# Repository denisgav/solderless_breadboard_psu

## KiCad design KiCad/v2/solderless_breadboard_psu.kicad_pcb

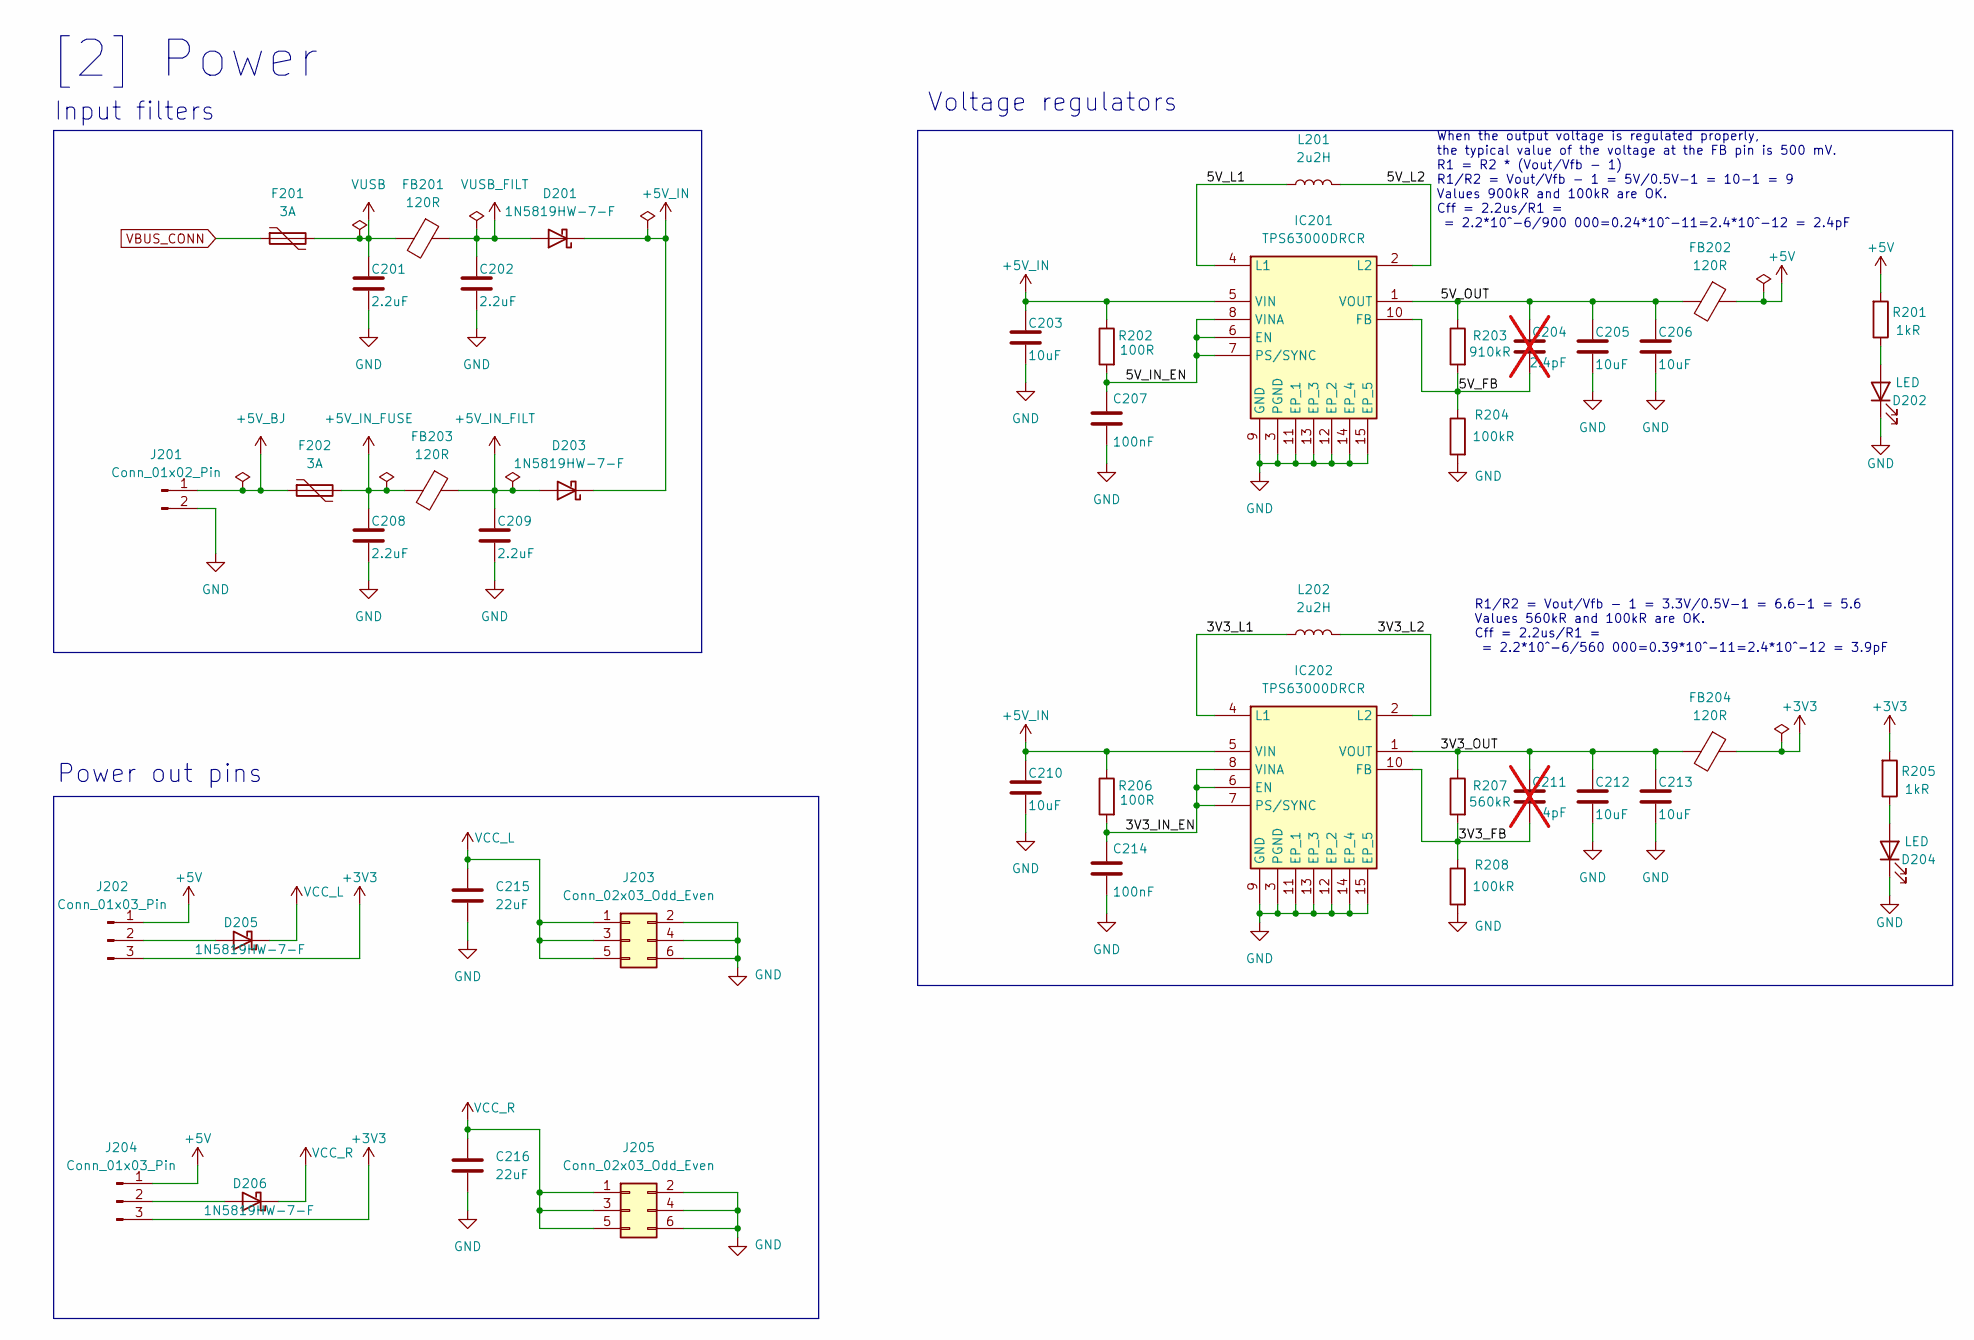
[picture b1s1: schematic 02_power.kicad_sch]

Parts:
C201, C202, C208, C209: 2.2uF; C_0603_1608Metric; Manufacturer Part Number CL10A225KO8NNNC; LCSC Part Number C23630
C203, C205, C206, C210, C212, C213: 10uF; C_0603_1608Metric; Manufacturer Part Number GRM188R61E106MA73D; LCSC Part Number C91606
C204: 2.4pF; C_0603_1608Metric; Manufacturer Part Number CC0603BRNPO9BN2R4; LCSC Part Number C519102; not fitted
C207, C214: 100nF; C_0402_1005Metric; Manufacturer Part Number GCM155R71H104KE02D; LCSC Part Number C85858
C211: 4pF; C_0603_1608Metric; not fitted
C215, C216: 22uF; C_0603_1608Metric; Manufacturer Part Number CL10A226MP8NUNE; DigiKey Part Number 1276-6687-6-ND
D201, D203, D205, D206: 1N5819HW-7-F; D_SOD-123; Manufacturer Part Number 1N5819HW-7-F; LCSC Part Number C82544
D202, D204: LED; LED_0603_1608Metric; Manufacturer Part Number XL-1608SURC-06; LCSC Part Number C965799
F201, F202: 3A; Fuse_0805_2012Metric; Manufacturer Part Number BSMD0805-100-6V; LCSC Part Number C883112
FB201, FB202, FB203, FB204: 120R; Fuse_0603_1608Metric; Manufacturer Part Number BLM18PG121SN1D; LCSC Part Number C14709
IC201, IC202: TPS63000DRCR; TPS63002DRCR; Manufacturer_Part_Number TPS63000DRCR; Mouser Part Number 595-TPS63000DRCR
J201: Conn_01x02_Pin; PinHeader_1x02_P2.54mm_Vertical
J202, J204: Conn_01x03_Pin; PinHeader_1x03_P2.54mm_Vertical
J203, J205: Conn_02x03_Odd_Even; PinHeader_2x03_P2.54mm_Vertical
L201, L202: 2u2H; L_Changjiang_FXL0630; Manufacturer Part Number FXL0630-2R2-M; LCSC Part Number C167218
R201, R205: 1kR; R_0402_1005Metric; Manufacturer Part Number RC0402FR-071KL; LCSC Part Number C106235
R202, R206: 100R; R_0402_1005Metric; Manufacturer Part Number RT0402BRD07100RL; LCSC Part Number C705627
R203: 910kR; R_0402_1005Metric; Manufacturer Part Number FRC0402F9103TS; LCSC Part Number C2909391
R204, R208: 100kR; R_0402_1005Metric; Manufacturer Part Number RT0402BRD07100KL; LCSC Part Number C852472
R207: 560kR; R_0402_1005Metric; Manufacturer Part Number 0402WGF5603TCE; LCSC Part Number C132339

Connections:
+3V3: FB204.1, J202.3, J204.3, R205.2
+5V: FB202.1, J202.1, J204.1, R201.2
+5V_BJ: F202.1, J201.1
+5V_IN: C203.1, C210.1, D201.1 (K), D203.1 (K), IC201.5 (VIN), IC202.5 (VIN), R202.1, R206.1
+5V_IN_FILT: C209.1, D203.2 (A), FB203.1
+5V_IN_FUSE: C208.1, F202.2, FB203.2
/[2] Power/3V3_FB: C211.2, IC202.10 (FB), R207.2, R208.1
/[2] Power/3V3_IN_EN: C214.1, IC202.6 (EN), IC202.7 (PS/SYNC), IC202.8 (VINA), R206.2
/[2] Power/3V3_L1: IC202.4 (L1), L202.1
/[2] Power/3V3_L2: IC202.2 (L2), L202.2
/[2] Power/3V3_OUT: C211.1, C212.1, C213.1, FB204.2, IC202.1 (VOUT), R207.1
/[2] Power/5V_FB: C204.2, IC201.10 (FB), R203.2, R204.1
/[2] Power/5V_IN_EN: C207.1, IC201.6 (EN), IC201.7 (PS/SYNC), IC201.8 (VINA), R202.2
/[2] Power/5V_L1: IC201.4 (L1), L201.1
/[2] Power/5V_L2: IC201.2 (L2), L201.2
/[2] Power/5V_OUT: C204.1, C205.1, C206.1, FB202.2, IC201.1 (VOUT), R203.1
GND: C201.2, C202.2, C203.2, C205.2, C206.2, C207.2, C208.2, C209.2, C210.2, C212.2, C213.2, C214.2, C215.2, C216.2, D202.1 (K), D204.1 (K), IC201.3 (PGND), IC201.9 (GND), IC201.11 (EP_1), IC201.12 (EP_2), IC201.13 (EP_3), IC201.14 (EP_4), IC201.15 (EP_5), IC202.3 (PGND), IC202.9 (GND), IC202.11 (EP_1), IC202.12 (EP_2), IC202.13 (EP_3), IC202.14 (EP_4), IC202.15 (EP_5), J201.2, J203.2, J203.4, J203.6, J205.2, J205.4, J205.6, R204.2, R208.2; also elsewhere on the board
unnamed: D202.2 (A), R201.1
unnamed: D204.2 (A), R205.1
unnamed: D205.2 (A), J202.2
unnamed: D206.2 (A), J204.2
VBUS_CONN: F201.1; also elsewhere on the board
VCC_L: C215.1, D205.1 (K), J203.1, J203.3, J203.5
VCC_R: C216.1, D206.1 (K), J205.1, J205.3, J205.5
VUSB: C201.1, F201.2, FB201.2; also elsewhere on the board
VUSB_FILT: C202.1, D201.2 (A), FB201.1; also elsewhere on the board

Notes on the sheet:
Input filters
Voltage regulators
When the output voltage is regulated properly, the typical value of the voltage at the FB pin is 500 mV. R1 = R2 * (Vout/Vfb - 1) R1/R2 = Vout/Vfb - 1 = 5V/0.5V-1 = 10-1 = 9 Values 900kR and 100kR are OK. Cff = 2.2us/R1 = = 2.2*10^-6/900 000=0.24*10^-11=2.4*10^-12 = 2.4pF
[2] Power
Power out pins
R1/R2 = Vout/Vfb - 1 = 3.3V/0.5V-1 = 6.6-1 = 5.6 Values 560kR and 100kR are OK. Cff = 2.2us/R1 = = 2.2*10^-6/560 000=0.39*10^-11=2.4*10^-12 = 3.9pF

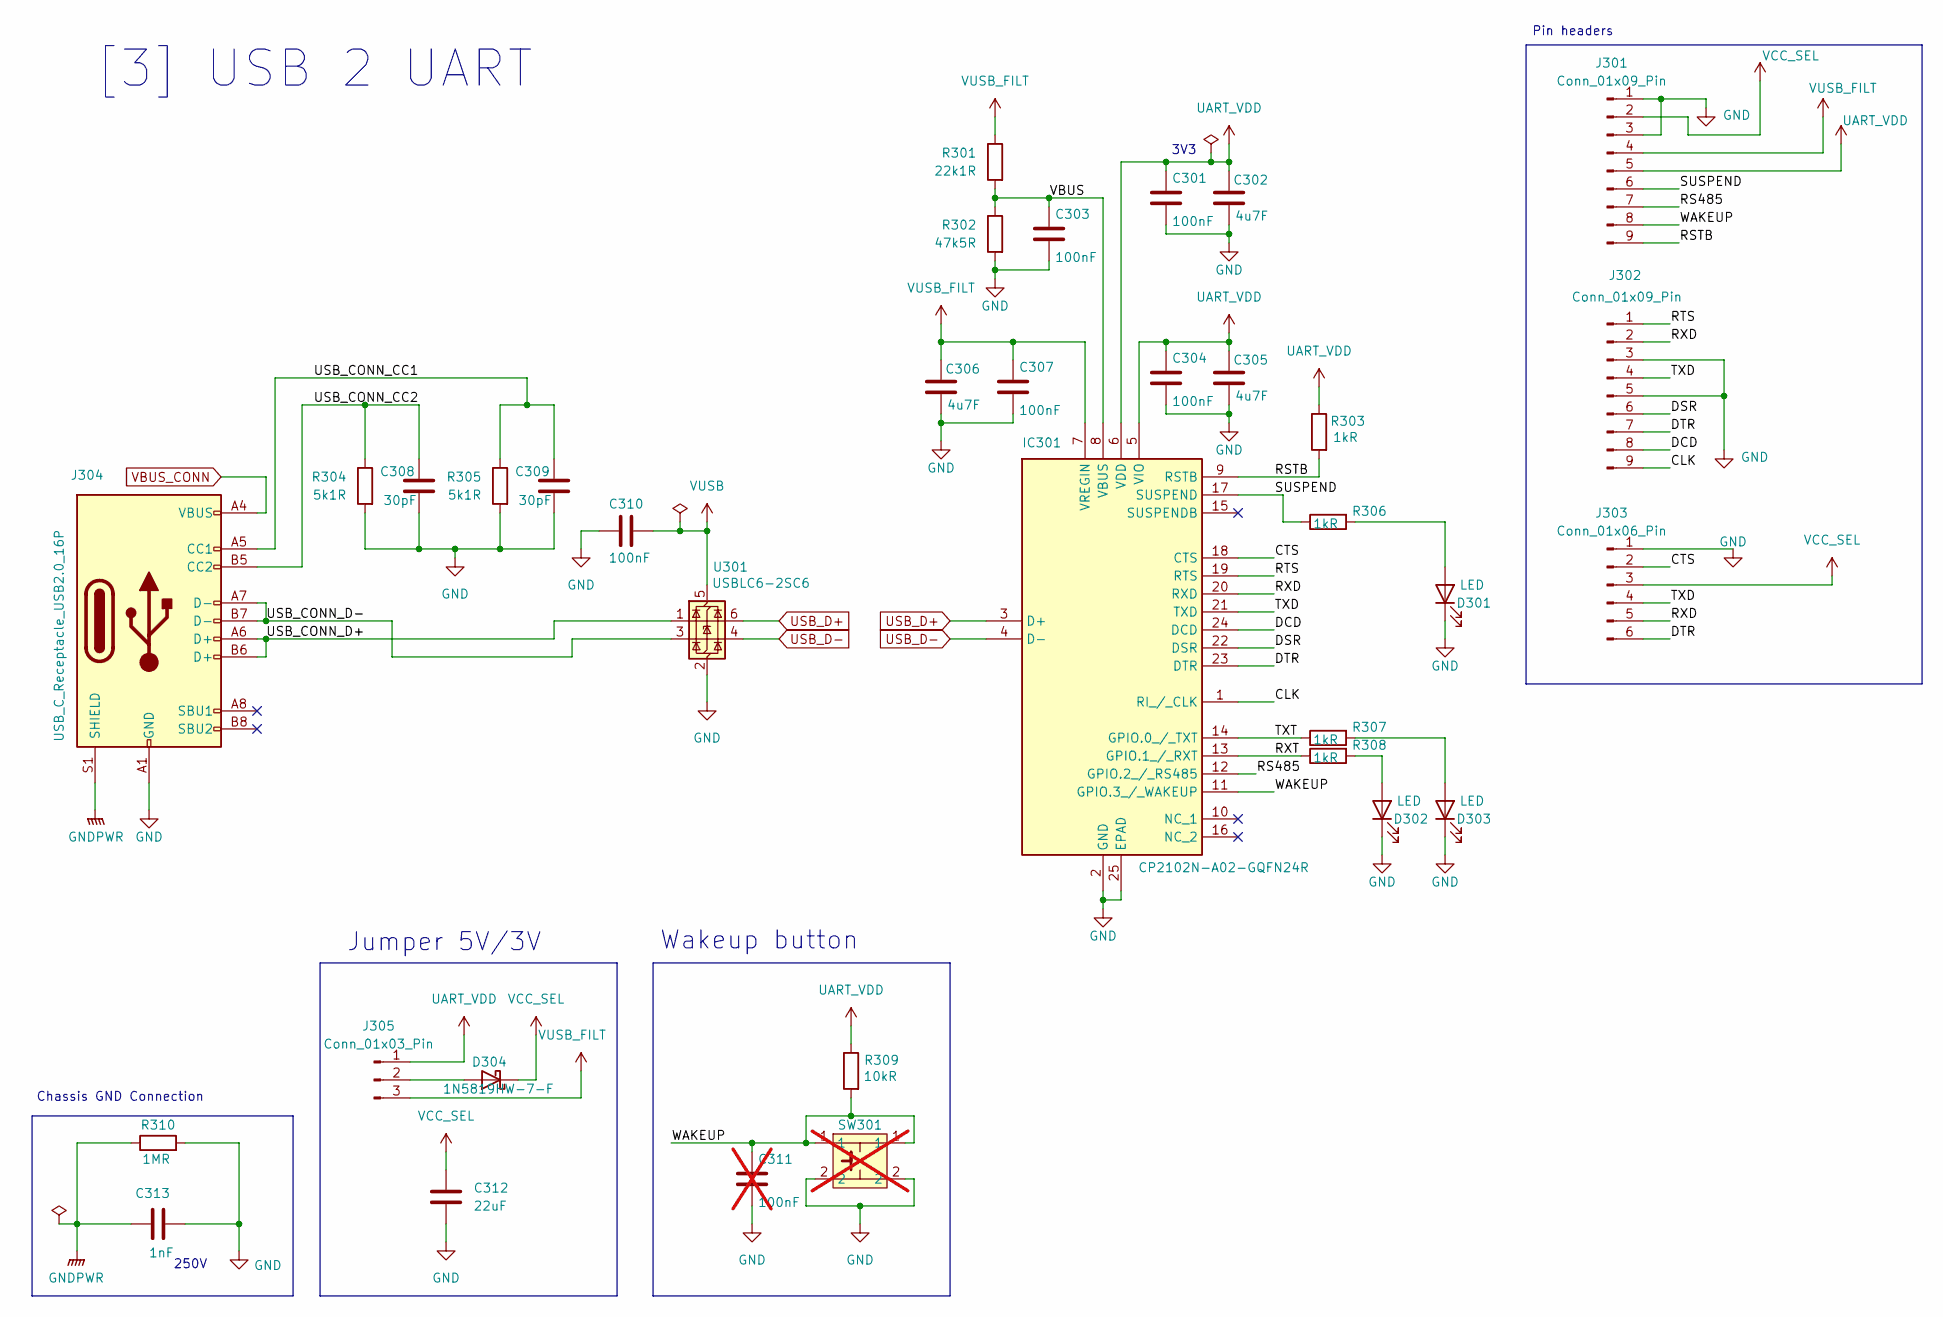
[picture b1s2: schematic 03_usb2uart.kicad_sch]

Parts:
C301, C303, C304, C307, C310: 100nF; C_0402_1005Metric; Manufacturer Part Number GCM155R71H104KE02D; LCSC Part Number C85858
C302, C305, C306: 4u7F; C_0603_1608Metric; Manufacturer Part Number CL10A475KP8NNNC; LCSC Part Number C1705
C308, C309: 30pF; C_0603_1608Metric; Manufacturer Part Number CC0603JRNPO9BN300; LCSC Part Number C113797
C311: 100nF; C_0402_1005Metric; Manufacturer Part Number GCM155R71H104KE02D; LCSC Part Number C85858; not fitted
C312: 22uF; C_0603_1608Metric; Manufacturer Part Number CL10A226MP8NUNE; DigiKey Part Number 1276-6687-6-ND
C313: 1nF; C_0603_1608Metric; Manufacturer Part Number CC0603KRX7R9BB102; LCSC Part Number C100040
D301, D302, D303: LED; LED_0603_1608Metric; Manufacturer Part Number XL-1608SURC-06; LCSC Part Number C965799
D304: 1N5819HW-7-F; D_SOD-123; Manufacturer Part Number 1N5819HW-7-F; LCSC Part Number C82544
IC301: CP2102N-A02-GQFN24R; QFN50P400X400X80-25N-D; Manufacturer_Part_Number CP2102N-A02-GQFN24R; Mouser Part Number 634-CP2102NA02QFN24R
J301, J302: Conn_01x09_Pin; PinHeader_1x09_P2.54mm_Vertical
J303: Conn_01x06_Pin; PinHeader_1x06_P2.54mm_Vertical
J304: USB_C_Receptacle_USB2.0_16P; USB_C_Receptacle_HCTL_HC-TYPE-C-16P-01A; Manufacturer Part Number TYPE-C-31-M-12; LCSC Part Number C165948
J305: Conn_01x03_Pin; PinHeader_1x03_P2.54mm_Vertical
R301: 22k1R; R_0402_1005Metric; Manufacturer Part Number CRCW040222K1FKED; LCSC Part Number C844504
R302: 47k5R; R_0402_1005Metric; Manufacturer Part Number RT0402DRE0747K5L; LCSC Part Number C853963
R303, R306, R307, R308: 1kR; R_0402_1005Metric; Manufacturer Part Number RC0402FR-071KL; LCSC Part Number C106235
R304, R305: 5k1R; R_0402_1005Metric; Manufacturer Part Number RT0402BRD075K1L; LCSC Part Number C852856
R309: 10kR; R_0402_1005Metric; Manufacturer Part Number CQ02WGF1002TCE; LCSC Part Number C2765610
R310: 1MR; R_0402_1005Metric; Manufacturer Part Number RE0402BRE071ML; LCSC Part Number C1883577
SW301: SW_PUSH_6mm_H5mm; Manufacturer Part Number SMG-01-H080A1; LCSC Part Number C29781314; not fitted
U301: USBLC6-2SC6; SOT-23-6; Manufacturer Part Number USBLC6-2SC6; LCSC Part Number C7519

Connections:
/[3] USB 2 UART/CLK: IC301.1 (RI_/_CLK), J302.9
/[3] USB 2 UART/CTS: IC301.18 (CTS), J303.2
/[3] USB 2 UART/DCD: IC301.24 (DCD), J302.8
/[3] USB 2 UART/DSR: IC301.22 (DSR), J302.6
/[3] USB 2 UART/DTR: IC301.23 (DTR), J302.7, J303.6
/[3] USB 2 UART/RS485: IC301.12 (GPIO.2_/_RS485), J301.7
/[3] USB 2 UART/RSTB: IC301.9 (RSTB), J301.9, R303.2
/[3] USB 2 UART/RTS: IC301.19 (RTS), J302.1
/[3] USB 2 UART/RXD: IC301.20 (RXD), J302.2, J303.5
/[3] USB 2 UART/RXT: IC301.13 (GPIO.1_/_RXT), R308.1
/[3] USB 2 UART/SUSPEND: IC301.17 (SUSPEND), J301.6, R306.1
/[3] USB 2 UART/TXD: IC301.21 (TXD), J302.4, J303.4
/[3] USB 2 UART/TXT: IC301.14 (GPIO.0_/_TXT), R307.1
/[3] USB 2 UART/USB_CONN_CC1: C309.1, J304.A5 (CC1), R305.1
/[3] USB 2 UART/USB_CONN_CC2: C308.1, J304.B5 (CC2), R304.1
/[3] USB 2 UART/USB_CONN_D+: J304.A6 (D+), J304.B6 (D+), U301.1 (I/O1)
/[3] USB 2 UART/USB_CONN_D-: J304.A7 (D-), J304.B7 (D-), U301.3 (I/O2)
/[3] USB 2 UART/VBUS: C303.1, IC301.8 (VBUS), R301.2, R302.1
/[3] USB 2 UART/WAKEUP: C311.1, IC301.11 (GPIO.3_/_WAKEUP), J301.8, R309.2, SW301.1
GND: C301.2, C302.2, C303.2, C304.2, C305.2, C306.2, C307.2, C308.2, C309.2, C310.2, C311.2, C312.2, C313.2, D301.1 (K), D302.1 (K), D303.1 (K), IC301.2 (GND), IC301.25 (EPAD), J301.1, J301.3, J302.3, J302.5, J303.1, J304.A1 (GND), J304.A12 (GND), J304.B1 (GND), J304.B12 (GND), R302.2, R304.2, R305.2, R310.2, SW301.2, U301.2 (GND); also elsewhere on the board
GNDPWR: C313.1, J304.S1 (SHIELD), R310.1
unnamed: D301.2 (A), R306.2
unnamed: D302.2 (A), R308.2
unnamed: D303.2 (A), R307.2
unnamed: D304.2 (A), J305.2
UART_VDD: C301.1, C302.1, C304.1, C305.1, IC301.5 (VIO), IC301.6 (VDD), J301.5, J305.1, R303.1, R309.1
USB_D+: IC301.3 (D+), U301.6 (I/O1)
USB_D-: IC301.4 (D-), U301.4 (I/O2)
VBUS_CONN: J304.A4 (VBUS), J304.A9 (VBUS), J304.B4 (VBUS), J304.B9 (VBUS); also elsewhere on the board
VCC_SEL: C312.1, D304.1 (K), J301.2, J303.3
VUSB: C310.1, U301.5 (VBUS); also elsewhere on the board
VUSB_FILT: C306.1, C307.1, IC301.7 (VREGIN), J301.4, J305.3, R301.1; also elsewhere on the board

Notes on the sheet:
Jumper 5V/3V
3V3
Pin headers
Wakeup button
Chassis GND Connection
250V
[3] USB 2 UART

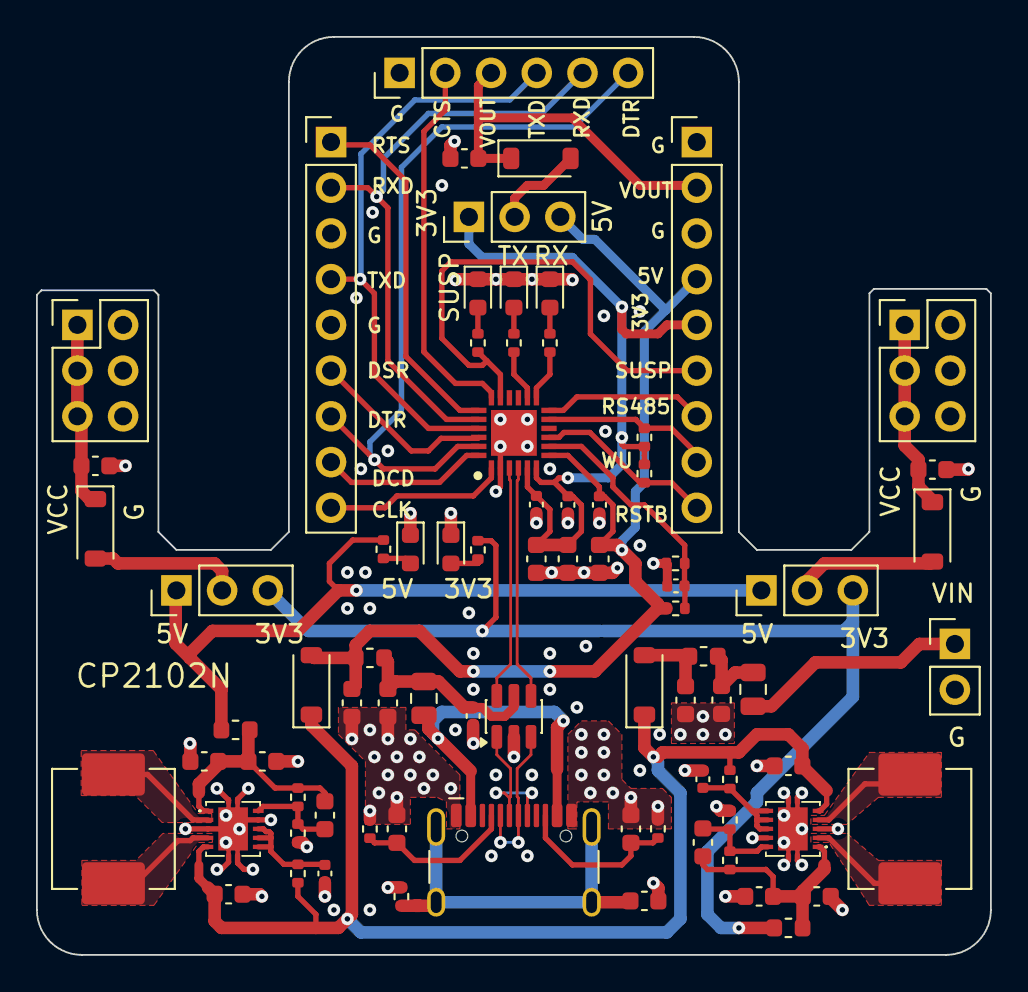
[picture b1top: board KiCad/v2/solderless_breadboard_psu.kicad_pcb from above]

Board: 4 copper layers, 53.0 x 51.0 mm, 78 parts (0 on the bottom side), 54 nets.

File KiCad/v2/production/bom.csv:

Designator,Footprint,Quantity,Value,LCSC Part #
"C201, C202, C208, C209",0603,4,2.2uF,C23630
"C203, C205, C206, C210, C212, C213",0603,6,10uF,C91606
C204,0603,1,2.4pF,C113797
"C207, C214, C301, C303, C304, C307, C310",0402,7,100nF,C126532
C211,0603,1,4pF,
"C215, C216, C312",0603,3,22uF,C86295
"C302, C305, C306",0603,3,4u7F,C1705
"C308, C309",0603,2,30pF,C113797
C313,0603,1,1nF,C277510
"D201, D203, D205, D206, D304",D_SOD-123,5,1N5819HW-7-F,C82544
"D202, D204, D301, D302, D303",0603,5,LED,C965799
"F201, F202",0805,2,3A,C883112
"FB201, FB202, FB203, FB204",0603,4,120R,C14709
"IC201, IC202",TPS63002DRCR,2,TPS63000DRCR,C116655
IC301,QFN50P400X400X80-25N-D,1,CP2102N-A02-GQFN24R,C969151
J201,PinHeader_1x02_P2.54mm_Vertical,1,Conn_01x02_Pin,
"J202, J204, J305",PinHeader_1x03_P2.54mm_Vertical,3,Conn_01x03_Pin,
"J203, J205",PinHeader_2x03_P2.54mm_Vertical,2,Conn_02x03_Odd_Even,
"J301, J302",PinHeader_1x09_P2.54mm_Vertical,2,Conn_01x09_Pin,
J303,PinHeader_1x06_P2.54mm_Vertical,1,Conn_01x06_Pin,
J304,USB_C_Receptacle_HCTL_HC-TYPE-C-16P-01A,1,USB_C_Receptacle_USB2.0_16P,C165948
"L201, L202",L_Changjiang_FXL0630,2,2u2H,C167218
"R201, R205, R303, R306, R307, R308",0402,6,1kR,C106235
"R202, R206",0402,2,100R,C705627
R203,0402,1,910kR,C2909391
"R204, R208",0402,2,100kR,C852472
R207,0402,1,560kR,C132339
R301,0402,1,22k1R,C844504
R302,0402,1,47k5R,C853963
"R304, R305",0402,2,5k1R,C852856
R309,0402,1,10kR,C2765610
R310,0402,1,1MR,C1883577
U301,SOT-23-6,1,USBLC6-2SC6,C7519

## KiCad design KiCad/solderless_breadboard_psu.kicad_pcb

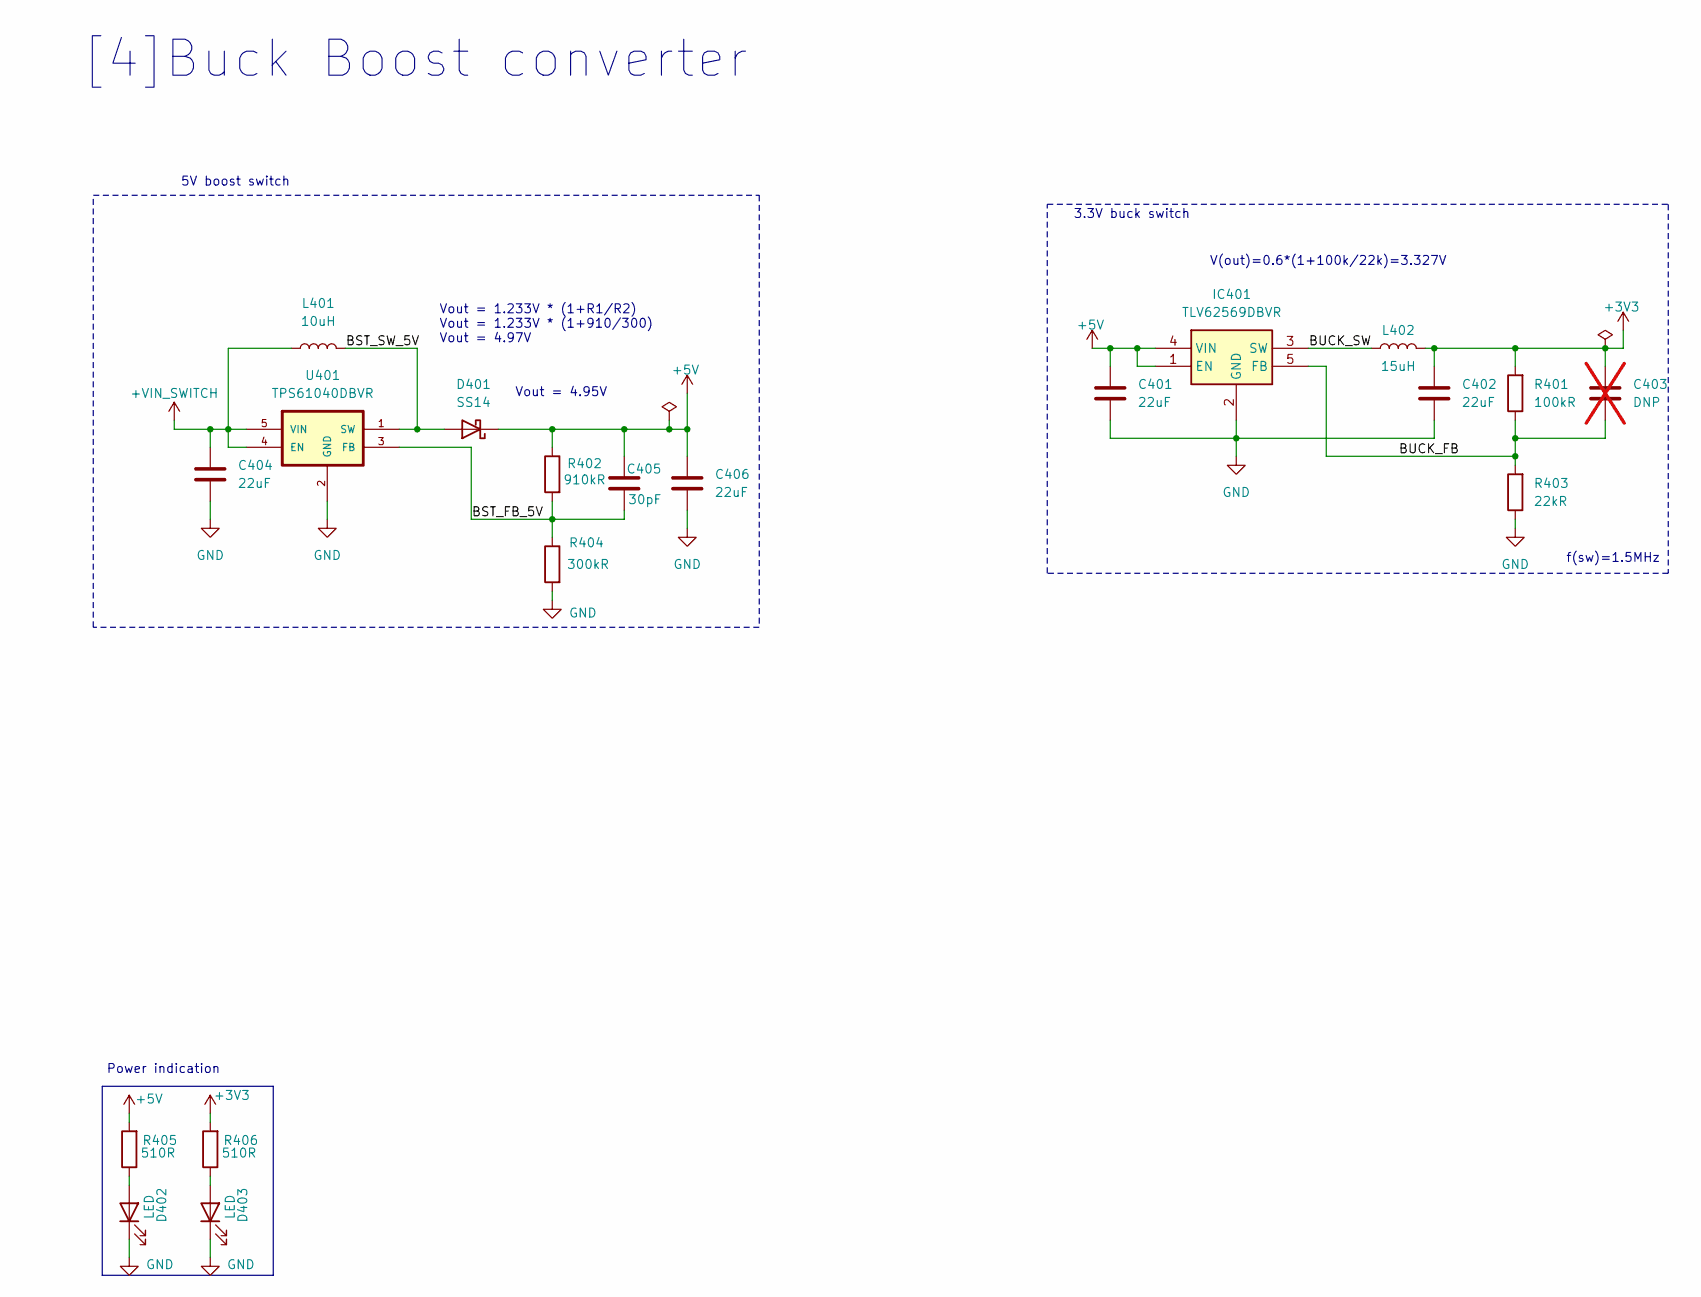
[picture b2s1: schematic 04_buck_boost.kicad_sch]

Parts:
C401, C402, C404, C406: 22uF; C_0603_1608Metric; Manufacturer Part Number CL10A226MP8NUNE; DigiKey Part Number 1276-6687-6-ND
C403: DNP; C_0402_1005Metric; not fitted
C405: 30pF; C_0603_1608Metric; Manufacturer Part Number CC0603JRNPO9BN300
D401: SS14; D_0603_1608Metric; Manufacturer Part Number SD0603S040S0R2
D402, D403: LED; LED_0603_1608Metric; Manufacturer Part Number XL-1608SURC-06
IC401: TLV62569DBVR; SOT95P280X145-5N; Manufacturer Part Number TLV62569DBVR
L401: 10uH; L_Changjiang_FXL0630; Manufacturer Part Number FXL0630-100-M
L402: 15uH; L_Changjiang_FXL0630; Manufacturer Part Number FXL0630-150-M; DigiKey Part Number 3442-MWSA0603S-150MTDKR-ND
R401: 100kR; R_0402_1005Metric; Manufacturer Part Number 0402WGF1003TCE; DigiKey Part Number P100KLDKR-ND
R402: 910kR; R_0402_1005Metric; Manufacturer Part Number 0402WGJ0914TCE
R403: 22kR; R_0402_1005Metric; Manufacturer Part Number 0402WGF2202TCE; DigiKey Part Number P22.0KLDKR-ND
R404: 300kR; R_0402_1005Metric; Manufacturer Part Number 0402WGF3003TCE
R405, R406: 510R; R_0402_1005Metric; Manufacturer Part Number 0402WGF5100TCE
U401: TPS61040DBVR; Manufacturer Part Number TPS61040DBVR

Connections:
+3V3: C402.1, C403.1, L402.2, R401.2, R406.2; also elsewhere on the board
+5V: C401.1, C405.1, C406.1, D401.1 (K), IC401.1 (EN), IC401.4 (VIN), R402.1, R405.2; also elsewhere on the board
+VIN_SWITCH: C404.1, L401.1, U401.4 (EN), U401.5 (VIN); also elsewhere on the board
/[4]Buck Boost converter/BST_FB_5V: C405.2, R402.2, R404.1, U401.3 (FB)
/[4]Buck Boost converter/BST_SW_5V: D401.2 (A), L401.2, U401.1 (SW)
/[4]Buck Boost converter/BUCK_FB: C403.2, IC401.5 (FB), R401.1, R403.2
/[4]Buck Boost converter/BUCK_SW: IC401.3 (SW), L402.1
GND: C401.2, C402.2, C404.2, C406.2, D402.1 (K), D403.1 (K), IC401.2 (GND), R403.1, R404.2, U401.2 (GND); also elsewhere on the board
unnamed: D402.2 (A), R405.1
unnamed: D403.2 (A), R406.1

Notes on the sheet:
Vout = 1.233V * (1+R1/R2) Vout = 1.233V * (1+910/300) Vout = 4.97V
[4]Buck Boost converter
Vout = 4.95V
3.3V buck switch
Power indication
V(out)=0.6*(1+100k/22k)=3.327V
f(sw)=1.5MHz
5V boost switch

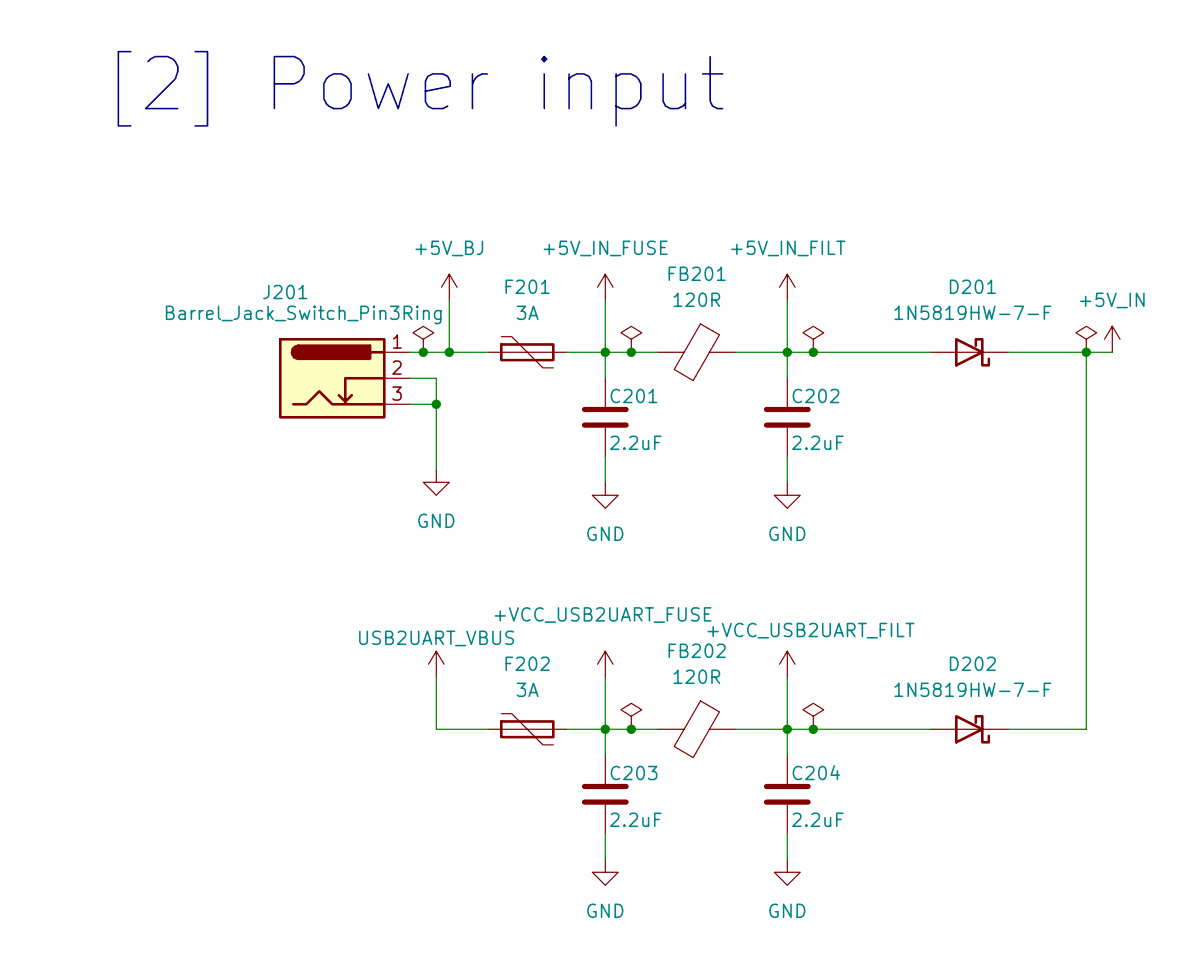
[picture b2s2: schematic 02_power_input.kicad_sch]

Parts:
C201, C202, C203, C204: 2.2uF; C_0603_1608Metric; Manufacturer Part Number CL10A225KO8NNNC
D201, D202: 1N5819HW-7-F; D_SOD-123; Manufacturer Part Number 1N5819HW-7-F
F201, F202: 3A; Fuse_0805_2012Metric; Manufacturer Part Number BSMD0805-100-6V
FB201, FB202: 120R; Fuse_0603_1608Metric; Manufacturer Part Number BLM18PG121SN1D
J201: Barrel_Jack_Switch_Pin3Ring; BarrelJack_GCT_DCJ200-10-A_Horizontal; Manufacturer Part Number DC005

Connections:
+5V_BJ: F201.1, J201.1
+5V_IN: D201.1 (K), D202.1 (K); also elsewhere on the board
+5V_IN_FILT: C202.1, D201.2 (A), FB201.1
+5V_IN_FUSE: C201.1, F201.2, FB201.2
+VCC_USB2UART_FILT: C204.1, D202.2 (A), FB202.1; also elsewhere on the board
+VCC_USB2UART_FUSE: C203.1, F202.2, FB202.2
GND: C201.2, C202.2, C203.2, C204.2, J201.2, J201.3; also elsewhere on the board
USB2UART_VBUS: F202.1; also elsewhere on the board

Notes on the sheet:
[2] Power input

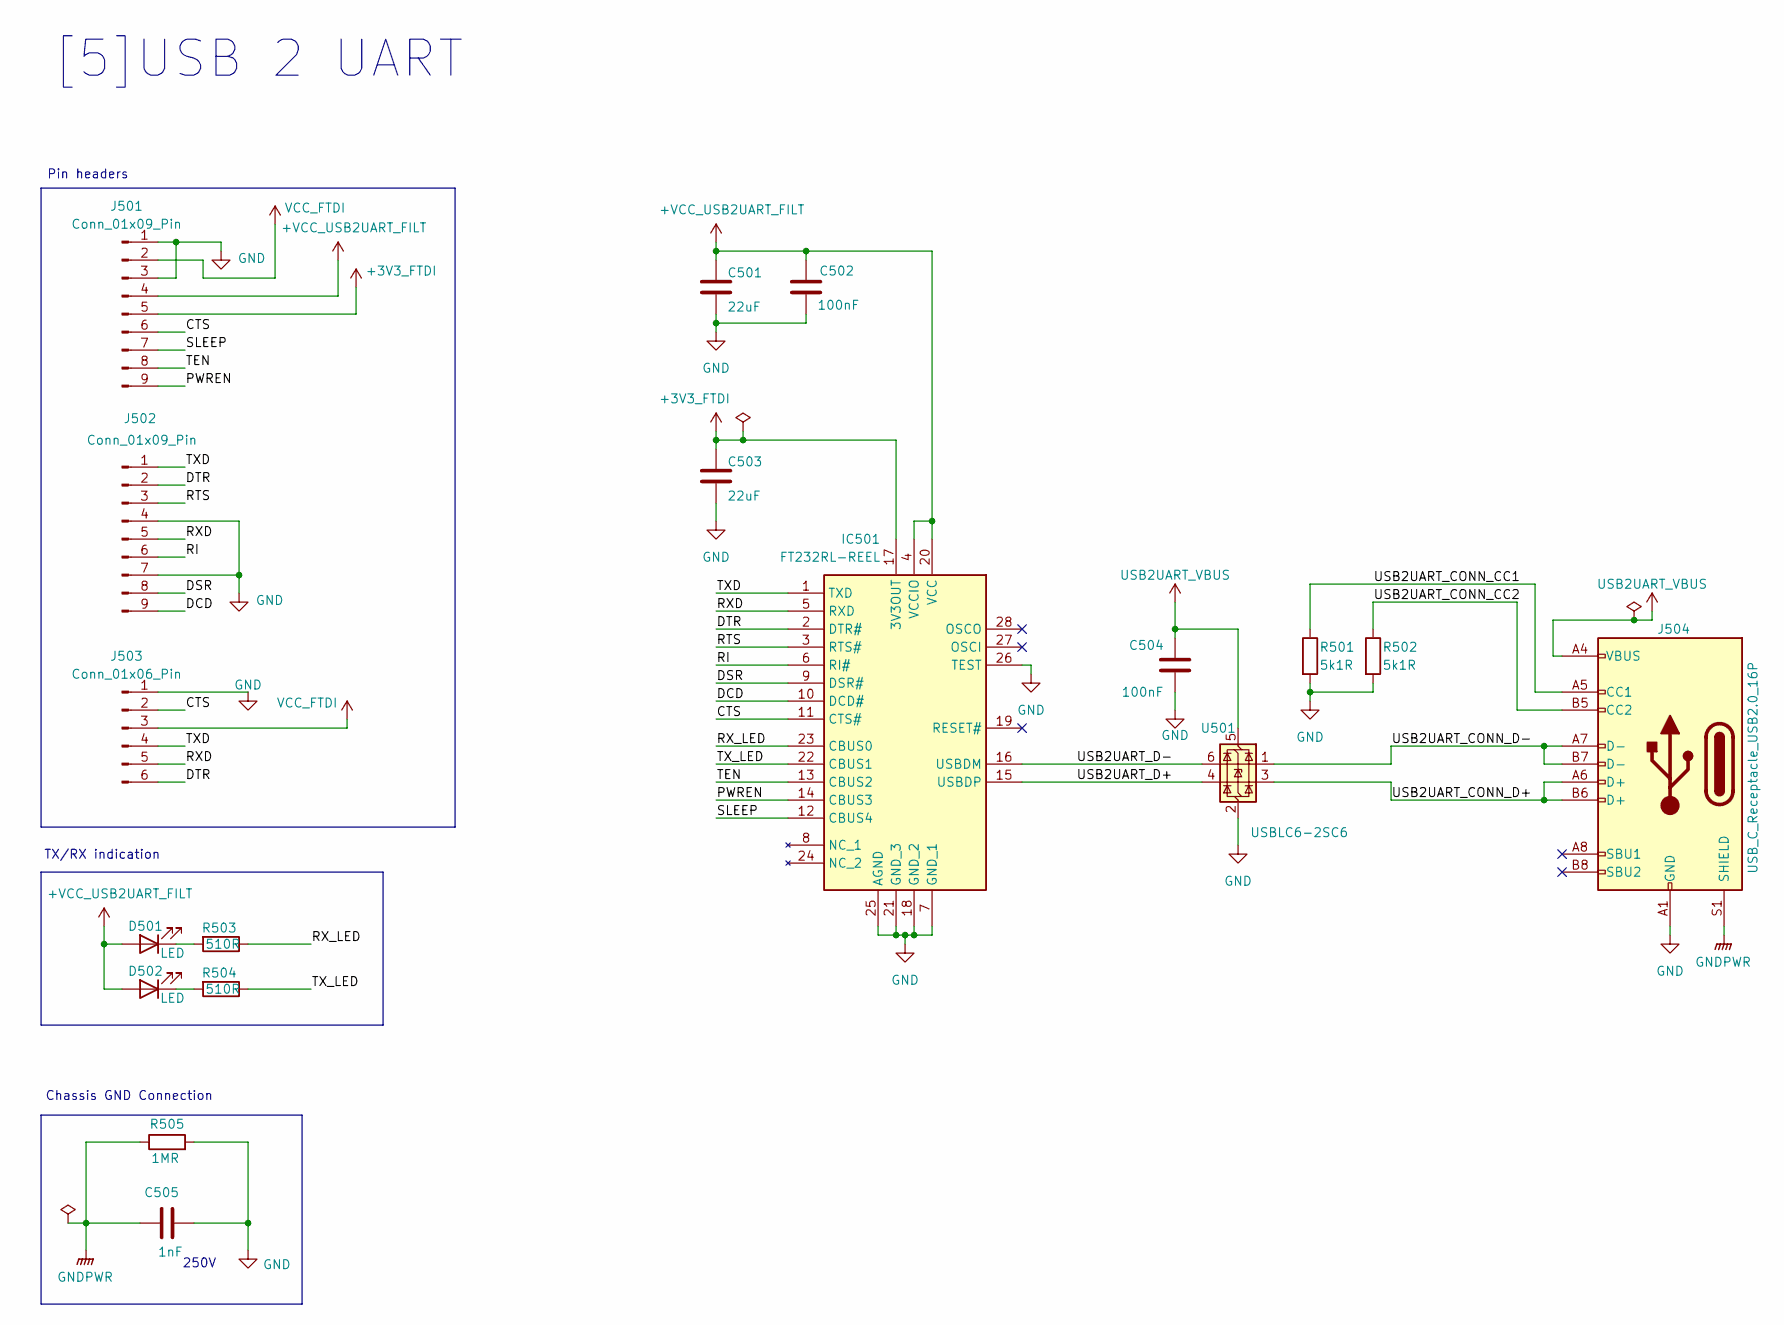
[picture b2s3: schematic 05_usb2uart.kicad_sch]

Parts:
C501, C503: 22uF; C_0603_1608Metric; Manufacturer Part Number CL10A226MP8NUNE; DigiKey Part Number 1276-6687-6-ND
C502, C504: 100nF; C_0402_1005Metric; Manufacturer Part Number CL05B104KO5NNNC; DigiKey Part Number 1276-1002-6-ND
C505: 1nF; C_0603_1608Metric; Manufacturer Part Number CC0603KRX7RYBB102
D501, D502: LED; LED_0603_1608Metric; Manufacturer Part Number XL-1608SURC-06
IC501: FT232RL-REEL; SOP65P778X200-28N; Manufacturer Part Number FT232RL-REEL
J501, J502: Conn_01x09_Pin; PinHeader_1x09_P2.54mm_Vertical
J503: Conn_01x06_Pin; PinHeader_1x06_P2.54mm_Vertical
J504: USB_C_Receptacle_USB2.0_16P; USB_C_Receptacle_HRO_TYPE-C-31-M-12; Manufacturer Part Number TYPE-C-31-M-12
R501, R502: 5k1R; R_0402_1005Metric; Manufacturer Part Number 0402WGF5101TCE
R503, R504: 510R; R_0402_1005Metric; Manufacturer Part Number 0402WGF5100TCE
R505: 1MR; R_0402_1005Metric; Manufacturer Part Number 0402WGF1004TCE
U501: USBLC6-2SC6; SOT-23-6; Manufacturer Part Number USBLC6-2SC6; DigiKey Part Number 497-5235-6-ND

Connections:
+3V3_FTDI: C503.1, IC501.17 (3V3OUT), J501.5; also elsewhere on the board
+VCC_USB2UART_FILT: C501.1, C502.1, D501.2 (A), D502.2 (A), IC501.4 (VCCIO), IC501.20 (VCC), J501.4; also elsewhere on the board
/[5]USB 2 UART/CTS: IC501.11 (CTS#), J501.6, J503.2
/[5]USB 2 UART/DCD: IC501.10 (DCD#), J502.9
/[5]USB 2 UART/DSR: IC501.9 (DSR#), J502.8
/[5]USB 2 UART/DTR: IC501.2 (DTR#), J502.2, J503.6
/[5]USB 2 UART/PWREN: IC501.14 (CBUS3), J501.9
/[5]USB 2 UART/RI: IC501.6 (RI#), J502.6
/[5]USB 2 UART/RTS: IC501.3 (RTS#), J502.3
/[5]USB 2 UART/RXD: IC501.5 (RXD), J502.5, J503.5
/[5]USB 2 UART/RX_LED: IC501.23 (CBUS0), R503.1
/[5]USB 2 UART/SLEEP: IC501.12 (CBUS4), J501.7
/[5]USB 2 UART/TEN: IC501.13 (CBUS2), J501.8
/[5]USB 2 UART/TXD: IC501.1 (TXD), J502.1, J503.4
/[5]USB 2 UART/TX_LED: IC501.22 (CBUS1), R504.1
/[5]USB 2 UART/USB2UART_CONN_CC1: J504.A5 (CC1), R501.1
/[5]USB 2 UART/USB2UART_CONN_CC2: J504.B5 (CC2), R502.1
/[5]USB 2 UART/USB2UART_CONN_D+: J504.A6 (D+), J504.B6 (D+), U501.3 (I/O2)
/[5]USB 2 UART/USB2UART_CONN_D-: J504.A7 (D-), J504.B7 (D-), U501.1 (I/O1)
/[5]USB 2 UART/USB2UART_D+: IC501.15 (USBDP), U501.4 (I/O2)
/[5]USB 2 UART/USB2UART_D-: IC501.16 (USBDM), U501.6 (I/O1)
GND: C501.2, C502.2, C503.2, C504.2, C505.2, IC501.7 (GND_1), IC501.18 (GND_2), IC501.21 (GND_3), IC501.25 (AGND), IC501.26 (TEST), J501.1, J501.3, J502.4, J502.7, J503.1, J504.A1 (GND), J504.A12 (GND), J504.B1 (GND), J504.B12 (GND), R501.2, R502.2, R505.2, U501.2 (GND); also elsewhere on the board
GNDPWR: C505.1, J504.S1 (SHIELD), R505.1
unnamed: D501.1 (K), R503.2
unnamed: D502.1 (K), R504.2
USB2UART_VBUS: C504.1, J504.A4 (VBUS), J504.A9 (VBUS), J504.B4 (VBUS), J504.B9 (VBUS), U501.5 (VBUS); also elsewhere on the board
VCC_FTDI: J501.2, J503.3; also elsewhere on the board

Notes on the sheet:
Chassis GND Connection
[5]USB 2 UART
Pin headers
250V
TX/RX indication
